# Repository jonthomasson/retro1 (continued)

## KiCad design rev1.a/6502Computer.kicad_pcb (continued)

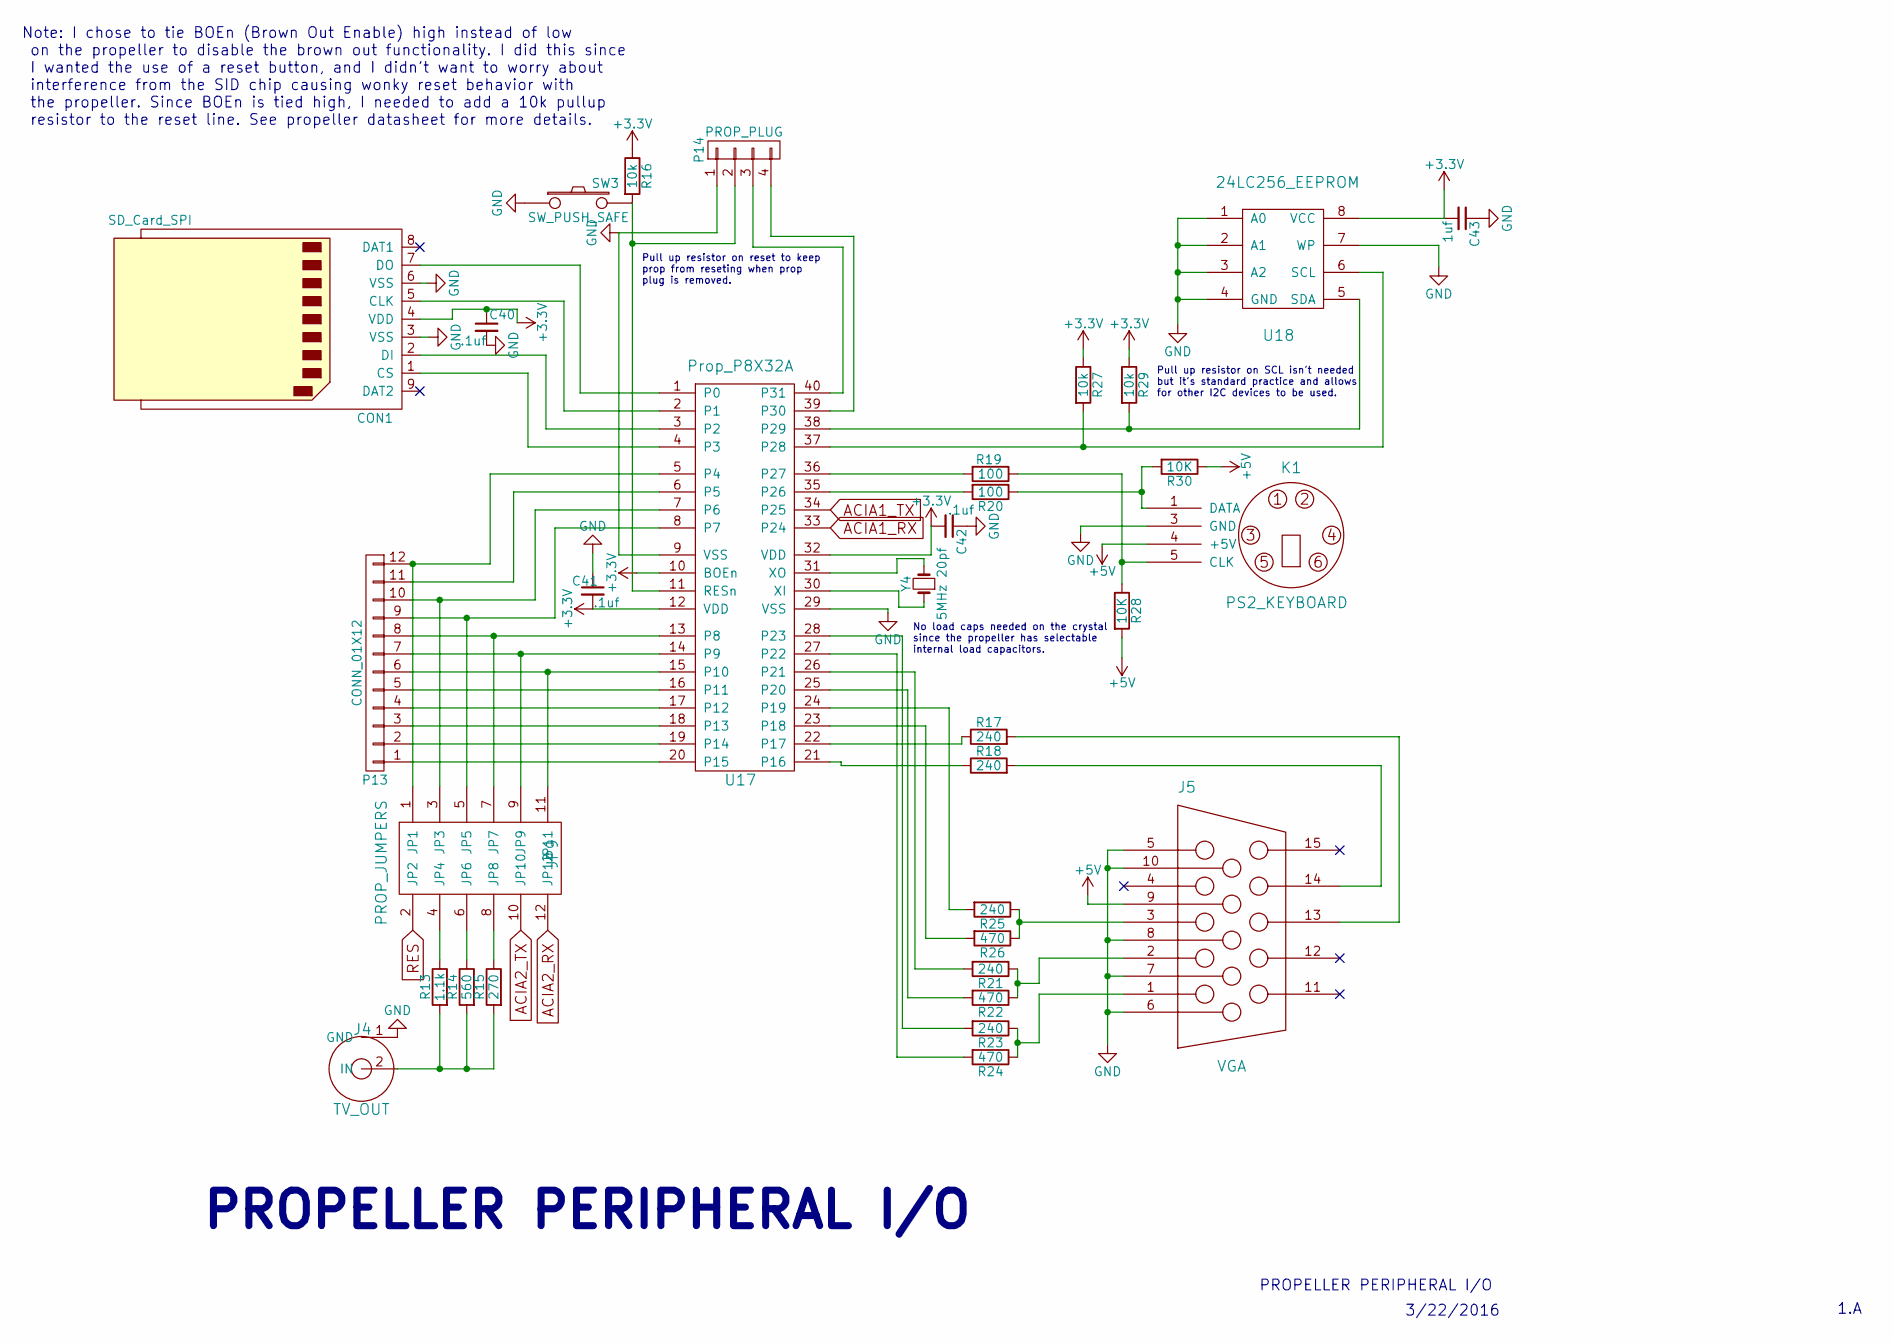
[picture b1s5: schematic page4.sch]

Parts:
C40, C41, C42: .1uf; C_Disc_D3_P2.5
C43: 1uf; C_Disc_D6_P5
CON1: SD_Card_SPI; DM1AASFPEJ_SDCARD
J4: TV_OUT; RCJ014VIDEO
J5: VGA; 117343442VGA
JP9: PROP_JUMPERS; Pin_Header_Straight_2x06
K1: PS2_KEYBOARD; MD60SM
P13: CONN_01X12; Socket_Strip_Straight_1x12
P14: PROP_PLUG
R13: 1.1k; Resistor_Horizontal_RM10mm
R14: 560; Resistor_Horizontal_RM10mm
R15: 270; Resistor_Horizontal_RM10mm
R16, R27, R29: 10k; Resistor_Horizontal_RM10mm
R17, R18, R21, R23, R25: 240; Resistor_Horizontal_RM10mm
R19, R20: 100; Resistor_Horizontal_RM10mm
R22, R24, R26: 470; Resistor_Horizontal_RM10mm
R28, R30: 10K; Resistor_Horizontal_RM10mm
SW3: SW_PUSH_SAFE; 1-1825027-1-TACTILE_SWITCH
U17: Prop_P8X32A; dil_40-600_socket
U18: 24LC256_EEPROM; dil_8-300_socket
Y4: 5MHz 20pf; crystal_hc-49s

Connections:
+3V3: C40.1, C41.2, C42.2, C43.2, CON1.4 (VDD), R16.1, R27.1, R29.1, U17.10 (BOEn), U17.12 (VDD), U17.32 (VDD), U18.8 (VCC); also elsewhere on the board
+5V: J5.9 (KEY/PWR), K1.4 (+5V), R28.2, R30.1; also elsewhere on the board
ACIA1_RX: U17.33 (P24); also elsewhere on the board
ACIA1_TX: U17.34 (P25); also elsewhere on the board
ACIA2_RX: JP9.12 (JP12); also elsewhere on the board
ACIA2_TX: JP9.10 (JP10); also elsewhere on the board
GND: C40.2, C41.1, C42.1, C43.1, CON1.3 (VSS), CON1.6 (VSS), J4.1 (GND), J5.5 (GND_HSYNC), J5.6 (RED_RTN), J5.7 (GREEN_RTN), J5.8 (BLUE_RTN), J5.10 (GND_VSYNC), K1.3 (GND), P14.1, SW3.1, U17.9 (VSS), U17.29 (VSS), U18.1 (A0), U18.2 (A1), U18.3 (A2), U18.4 (GND), U18.7 (WP); also elsewhere on the board
unnamed: CON1.1 (CS), U17.4 (P3)
unnamed: CON1.2 (DI), U17.3 (P2)
unnamed: CON1.5 (CLK), U17.2 (P1)
unnamed: CON1.7 (DO), U17.1 (P0)
unnamed: J4.2 (IN), R13.2, R14.2, R15.2
unnamed: J5.1 (RED), R23.1, R24.1
unnamed: J5.2 (GREEN), R21.1, R22.1
unnamed: J5.3 (BLUE), R25.1, R26.1
unnamed: J5.13 (HSYNC), R17.2
unnamed: J5.14 (VSYNC), R18.2
unnamed: JP9.1 (JP1), P13.12, U17.5 (P4)
unnamed: JP9.3 (JP3), P13.10, U17.7 (P6)
unnamed: JP9.4 (JP4), R13.1
unnamed: JP9.5 (JP5), P13.9, U17.8 (P7)
unnamed: JP9.6 (JP6), R14.1
unnamed: JP9.7 (JP7), P13.8, U17.13 (P8)
unnamed: JP9.8 (JP8), R15.1
unnamed: JP9.9 (JP9), P13.7, U17.14 (P9)
unnamed: JP9.11 (JP11), P13.6, U17.15 (P10)
unnamed: K1.1 (DATA), R20.1, R30.2
unnamed: K1.5 (CLK), R19.1, R28.1
unnamed: P13.1, U17.20 (P15)
unnamed: P13.2, U17.19 (P14)
unnamed: P13.3, U17.18 (P13)
unnamed: P13.4, U17.17 (P12)
unnamed: P13.5, U17.16 (P11)
unnamed: P13.11, U17.6 (P5)
unnamed: P14.2, R16.2, SW3.4, U17.11 (RESn)
unnamed: P14.3, U17.40 (P31)
unnamed: P14.4, U17.39 (P30)
unnamed: R17.1, U17.22 (P17)
unnamed: R18.1, U17.21 (P16)
unnamed: R19.2, U17.36 (P27)
unnamed: R20.2, U17.35 (P26)
unnamed: R21.2, U17.26 (P21)
unnamed: R22.2, U17.25 (P20)
unnamed: R23.2, U17.28 (P23)
unnamed: R24.2, U17.27 (P22)
unnamed: R25.2, U17.24 (P19)
unnamed: R26.2, U17.23 (P18)
unnamed: R27.2, U17.37 (P28), U18.6 (SCL)
unnamed: R29.2, U17.38 (P29), U18.5 (SDA)
unnamed: U17.30 (XI), Y4.1
unnamed: U17.31 (XO), Y4.2
RES: JP9.2 (JP2); also elsewhere on the board

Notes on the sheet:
PROPELLER PERIPHERAL I/O
Note: I chose to tie BOEn (Brown Out Enable) high instead of low on the propeller to disable the brown out functionality. I did this since I wanted the use of a reset button, and I didn't want to worry about interference from the SID chip causing wonky reset behavior with the propeller. Since BOEn 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
No load caps needed on the crystal since the propeller has selectable internal load capacitors.
Pull up resistor on SCL isn't needed but it's standard practice and allows for other I2C devices to be used.
Pull up resistor on reset to keep prop from reseting when prop plug is removed.
3/22/2016
1.A

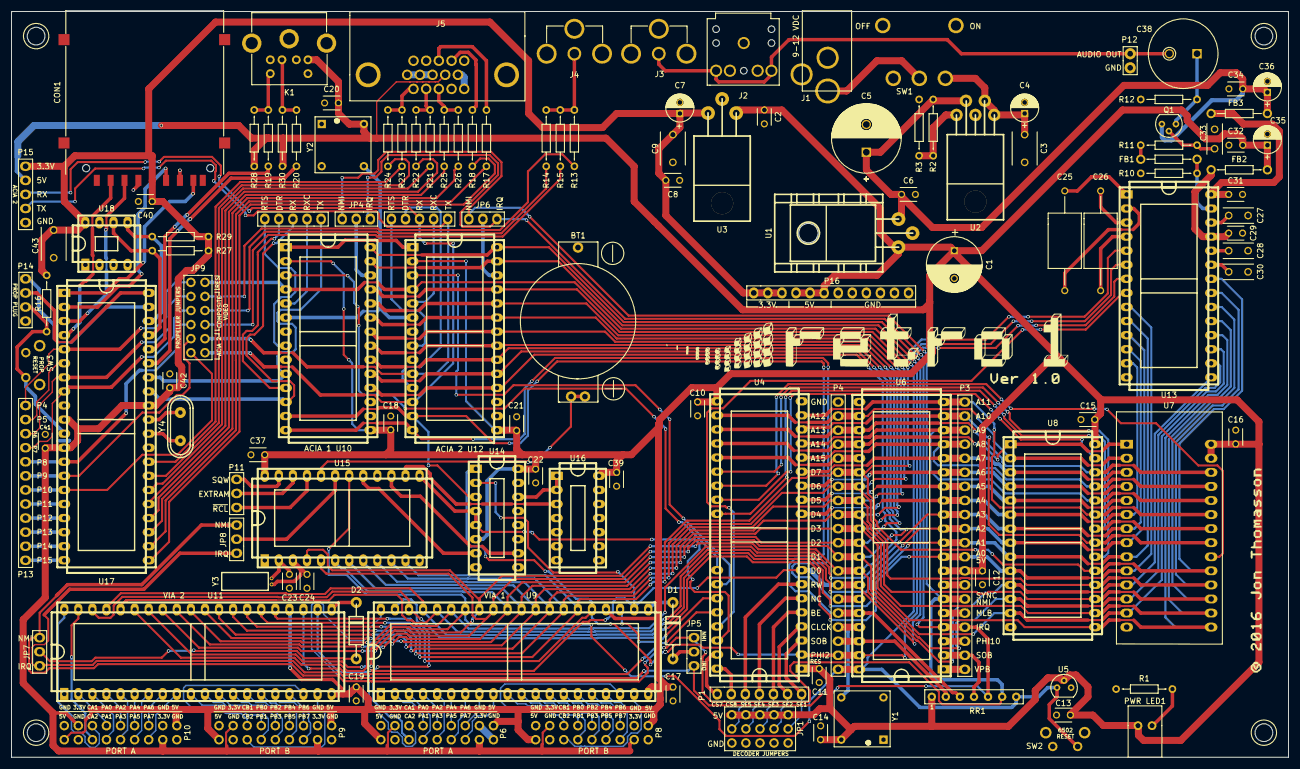
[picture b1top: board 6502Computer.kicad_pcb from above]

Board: 2 copper layers, 230.5 x 134.6 mm, 130 parts (0 on the bottom side), 189 nets.

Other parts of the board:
ACIA 1 U10, ACIA 2 U12: 6551; dil_28-600_socket
PWR LED1: LED; WP1503CB_LED

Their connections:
+5V: ACIA 1 U10.2, ACIA 1 U10.15, ACIA 2 U12.2, ACIA 2 U12.15, PWR LED1.2; also elsewhere on the board
/page 2/D0: ACIA 1 U10.18, ACIA 2 U12.18; also elsewhere on the board
/page 2/D1: ACIA 1 U10.19, ACIA 2 U12.19; also elsewhere on the board
/page 2/D2: ACIA 1 U10.20, ACIA 2 U12.20; also elsewhere on the board
/page 2/D3: ACIA 1 U10.21, ACIA 2 U12.21; also elsewhere on the board
/page 2/D4: ACIA 1 U10.22, ACIA 2 U12.22; also elsewhere on the board
/page 2/D5: ACIA 1 U10.23, ACIA 2 U12.23; also elsewhere on the board
/page 2/D6: ACIA 1 U10.24, ACIA 2 U12.24; also elsewhere on the board
/page 2/D7: ACIA 1 U10.25, ACIA 2 U12.25; also elsewhere on the board
A0: ACIA 1 U10.13, ACIA 2 U12.13; also elsewhere on the board
A1: ACIA 1 U10.14, ACIA 2 U12.14; also elsewhere on the board
ACIA1_RX: ACIA 1 U10.12; also elsewhere on the board
ACIA1_TX: ACIA 1 U10.10; also elsewhere on the board
ACIA2_RX: ACIA 2 U12.12; also elsewhere on the board
ACIA2_TX: ACIA 2 U12.10; also elsewhere on the board
CS_ACIA1: ACIA 1 U10.3; also elsewhere on the board
CS_ACIA2: ACIA 2 U12.3; also elsewhere on the board
GND: ACIA 1 U10.1, ACIA 1 U10.9, ACIA 1 U10.16, ACIA 1 U10.17, ACIA 2 U12.1, ACIA 2 U12.9, ACIA 2 U12.16, ACIA 2 U12.17; also elsewhere on the board
unnamed 91: ACIA 1 U10.26; also elsewhere on the board
unnamed 92: ACIA 2 U12.26; also elsewhere on the board
unnamed 105: PWR LED1.1; also elsewhere on the board
unnamed 106: ACIA 1 U10.5; also elsewhere on the board
unnamed 107: ACIA 1 U10.11; also elsewhere on the board
unnamed 108: ACIA 1 U10.8; also elsewhere on the board
unnamed 109: ACIA 2 U12.5; also elsewhere on the board
unnamed 110: ACIA 2 U12.11; also elsewhere on the board
unnamed 111: ACIA 2 U12.8; also elsewhere on the board
unnamed 137: ACIA 1 U10.6, ACIA 2 U12.6; also elsewhere on the board
PHI2: ACIA 1 U10.27, ACIA 2 U12.27; also elsewhere on the board
RES: ACIA 1 U10.4, ACIA 2 U12.4; also elsewhere on the board
RW: ACIA 1 U10.28, ACIA 2 U12.28; also elsewhere on the board

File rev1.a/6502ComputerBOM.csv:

"Id";"Designator";"Package";"Quantity";"Designation";"Supplier and ref";
1;"U6";"dil_40-600_socket";1;"65C02";;;
2;"Y4";"crystal_hc-49s";1;"5MHz 20pf";;;
3;"D2,D1";"diode_do41";2;"1N5817";;;
4;"Y1";"ECS-2100AX";1;"ECS-2100X-1MHZ";;;
5;"ACIA 1 U10,ACIA 2 U12";"dil_28-600_socket";2;"6551";;;
6;"REF**,REF**,REF**,REF**";"1pin";4;"1pin";;;
7;"J1";"Barrel_Jack_PJ002A";1;"BARREL_JACK";;;
8;"BT1";"BU2032SM";1;"CR2032 3V";;;
9;"C1";"C_Radial_D10_L16_P5";1;"1000uf";;;
10;"C2,C6,C8,C10,C11,C12,C13,C14,C15,C16,C17,C18,C19,C20,C21,C22,C37,C39,C40,C41,C42";"C_Disc_D3_P2.5";21;".1uf";;;
11;"C3,C9";"C_Disc_D6_P5";2;".33uf";;;
12;"C4,C7";"C_Radial_D5_L11_P2";2;"47uf";;;
13;"C5";"C_Radial_D12.5_L25_P5";1;"1000uf";;;
14;"C25,C26";"C_Axial_D6_L11_P18";2;"2.2nf";;;
15;"C29";"C_Disc_D3_P2.5";1;".22uf";;;
16;"C31";"C_Disc_D3_P2.5";1;".47uf";;;
17;"C32,C34";"C_Disc_D3_P2.5";2;".47nf";;;
18;"C35,C36";"C_Radial_D5_L11_P2";2;"10uf";;;
19;"C38";"C_Radial_D12.5_L25_P5";1;"10uf";;;
20;"C43";"C_Disc_D6_P5";1;"1uf";;;
21;"CON1";"DM1AASFPEJ_SDCARD";1;"SD_Card_SPI";;;
22;"FB1,FB2,FB3";"Ferrite_Bead_Horizontal_RM10mm";3;"FB";;;
23;"J2";"SJ13525NHeadphone";1;"JACK_2P";;;
24;"J3";"RCJ013AUDIO";1;"AUDIO_OUT";;;
25;"J4";"RCJ014VIDEO";1;"TV_OUT";;;
26;"JP1";"Pin_Header_Straight_3x05";1;"DECODER_JUMPERS";;;
27;"JP4,JP5,JP6,JP7,JP8";"Pin_Header_Straight_1x03";5;"JUMPER3";;;
28;"K1";"MD60SM";1;"PS2_KEYBOARD";;;
29;"P3,P4";"Socket_Strip_Straight_1x20";2;"CONN_01X20";;;
30;"P5,P7";"Socket_Strip_Straight_1x05";2;"CONN_01X05";;;
31;"P6,P8,P9,P10";"Socket_Strip_Angled_2x09";4;"CONN_02X09";;;
32;"P11";"Socket_Strip_Straight_1x03";1;"CONN_01X03";;;
33;"P12";"Socket_Strip_Straight_1x02";1;"CONN_01X02";;;
34;"P13,P16";"Socket_Strip_Straight_1x12";2;"CONN_01X12";;;
35;"P14";"PROP_PLUG";1;"PROP_PLUG";;;
36;"Q1";"TO-92_Molded_Narrow";1;"2N2222A";;;
37;"R1";"Resistor_Horizontal_RM10mm";1;"330";;;
38;"R2";"Resistor_Horizontal_RM10mm";1;"422k";;;
39;"R3";"Resistor_Horizontal_RM10mm";1;"53.6k";;;
40;"R10,R12";"Resistor_Horizontal_RM10mm";2;"1k";;;
41;"R11,R16,R27,R29";"Resistor_Horizontal_RM10mm";4;"10k";;;
42;"R13";"Resistor_Horizontal_RM10mm";1;"1.1k";;;
43;"R14";"Resistor_Horizontal_RM10mm";1;"560";;;
44;"R15";"Resistor_Horizontal_RM10mm";1;"270";;;
45;"R17,R18,R21,R23,R25";"Resistor_Horizontal_RM10mm";5;"240";;;
46;"R19,R20";"Resistor_Horizontal_RM10mm";2;"100";;;
47;"R22,R24,R26";"Resistor_Horizontal_RM10mm";3;"470";;;
48;"R28,R30";"Resistor_Horizontal_RM10mm";2;"10K";;;
49;"U1";"to220-horiz_5772";1;"MIC29150-5.0WT";;;
50;"U2";"to220-5-horiz-notab";1;"MIC29152WT";;;
51;"U3";"to220-horiz-notab";1;"MIC29150-3.3WT";;;
52;"U5";"TO-92_Molded_Narrow";1;"DS1813_EconoReset";;;
53;"U8";"dil_28-600_socket";1;"62256_SRAM";;;
54;"U9,U11";"dil_40-600_socket";2;"6522";;;
55;"U13";"dil_28-600_socket";1;"6581_SID";;;
56;"U14";"dil_16-300_socket";1;"74LS138N";;;
57;"U15";"dil_24-600_socket";1;"BQ3285E_RTC";;;
58;"U16";"dil_14-300_socket";1;"7400";;;
59;"U17";"dil_40-600_socket";1;"Prop_P8X32A";;;
60;"U18";"dil_8-300_socket";1;"24LC256_EEPROM";;;
61;"Y3";"crystal_tc-38_horiz";1;"32.768kHz";;;
62;"U7";"28-526-11-SOCKET";1;"AT28C256_EEPROM";;;
63;"SW2,SW3";"1-1825027-1-TACTILE_SWITCH";2;"SW_PUSH_SAFE";;;
64;"PWR LED1";"WP1503CB_LED";1;"LED";;;
65;"JP9";"Pin_Header_Straight_2x06";1;"PROP_JUMPERS";;;
66;"P15";"Pin_Header_Angled_1x05";1;"CONN_01X05";;;
67;"C27,C28,C30,C33";"C_Disc_D6_P3.5_Skinny";4;"1nf";;;
68;"RR1";"7_pin_resistor_network";1;"RR7";;;
69;"C23,C24";"C_Disc_D3_P2.5";2;"6pf";;;
70;"SW1";"SW_Micro_Right_Angle_SPST";1;"SPST2";;;
71;"J5";"117343442VGA";1;"VGA";;;
72;"P1";"Socket_Strip_Straight_1x07";1;"CONN_01X07";;;
73;"G***";"retro1";1;"LOGO";;;
74;"G***";"copyright";1;"LOGO";;;
75;"U4";"Address_Decoder_CPLD2";1;"AddressDecoderModule";;;
76;"Y2";"ECS-2100AX";1;"1.8432MHZ_OSC";;;

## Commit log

2017-04-14 :space_invader: Added .gitattributes & .gitignore files
2017-04-17 initial software checkin
2017-04-17 propeller terminal code
